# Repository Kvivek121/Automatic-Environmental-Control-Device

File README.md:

# Automatic-Environmental-Control-Device

1.Project details ---------------------------------------------------------------------1
	(– Problem Statement / Objectives / Expectations / Working principle)
2.Design consideration containing------------------------------------------------2
	a. Block diagram -----------------------------------------------------------------2
	a.Selection criteria -------------------------------------------------------------2
	b.Calculation for components ------------------------------------------------7
	c.Firmware consideration  ----------------------------------------------------7
	d.Firmware block diagram / Flow chart ------------------------------------8
	e.Test plan  --------------------------------------------------------------------10
3.Component values and part number ------------------------------------------11
4.Circuit simulation ---------------------------------------------------------------12
5.Simulation results ---------------------------------------------------------------12
6.Test Reports ----------------------------------------------------------------------14
7.Conclusion------------------------------------------------------------------------14

1.	Project details: -

•	Project Title: -Automatic Environment Control device
•	Problem Statement: - To develop an Industrial automation device which will operate certain functionalities based on the various Environmental parameters (Temperature, Pressure and Humidity level) of a Container/Room.

•	Project Objectives: - 
i.	Sense the Temperature, Humidity and Pressure from BMP280 and DHT11 sensor.
ii.	Take measure to control the Environmental parameter if the value crosses a certain limit.
iii.	Provide a functionality to user to change the Threshold values of Environmental parameters through a switch.
iv.	Display the Sensed value of temperature, Humidity, pressure.  

Working: - The Automatic environmental control device work on the principle of acquisition of sensory data from the environment and process them, based on set threshold by the user the various environmental control measures can be taken to control the environmental parameters up to the desired limit. On booting up of the device the 16x2  LCD display welcome message after this  BMP280 temperature and pressure sensor and DHT11digital  humidity and temperature sensor start sensing the various environmental parameter , STM32f103C8t6 based microcontroller communicate with the  sensors through different Communication protocols like SPI with BMP 280 and digital read for DHT 11 sensor based on the set algorithm the raw values of the sensors are converted into useful data and simultaneously the process data is displayed on the 16x2 LCD display which is using I2C  protocol for communication with the microcontroller. Sensors are directly been powered from microcontroller which is been powered by a 9 volt battery,  the user also get three switches which are used to generate interrupt the first switch is a menu switch the second switch increment the threshold and the third switch is to decrement the threshold when the user press the menu button the program enter into a menu program based on the number of times user press the menu button the functionality changes, if the user presses button once temperature threshold update menu open while for two pressure update menu and for three Humidity threshold update menu. If the user presses five times the program returns back to the Main program where the continuous measurement of the environmental parameter is taking. 
If a particular parameter viz. temperature, pressure or humidity exceeds the set threshold value, a trigger to the   relay circuitry is generated which is separated by an opto-isolator. Relay circuitry operates the environmental control measures, for example if temperature of a room increases above a set threshold value the air conditioner or a fan can be operated similarly if Humidity exceeds a certain limit dry air can be pumped in and if pressure is increased above a certain limit the Chamber can be pressurized or de-pressurized based on the requirement.
	2. Design consideration containing
	
a.	 Block diagram 

General Device Block diagram

b.	Selection criteria 
The various components are selected based on the required functionality, easy availability, cost and pression up to which the sensor can provide the output, below is the detailed selection criterion and the available alternatives in the market. 

1.	Microcontroller: - STM32f103c8t6 is used in the project to collect the sensory inputs from BMP280 and DHT11 sensor which work on SPI and digital input interfaces, while and 16X2 LCD with an I2C extender is used which uses I2C protocol for communication.
Blue pill provides SPI, I2C ports and digital I/O pins and Timers with 64KB Flash and 20KB of SRAM which satisfied the need for the application with minimum wastage of resources.
Available alternatives: - A range of Microcontrollers board by STM32, PIC, Arduino, Espressif, Raspberry pi are available. The closest alternative was the STM32f103c6t6 board but due to only 32Kbytes of Flash available the board was not capable to handle the Firmware.
2.	Sensor: - The sensors used in the project are Temperature, Humidity and Pressure sensor.

i.	Temperature -BMP280 sensor by Bosch is used which is a Barometric pressure and temperature measurement sensor. DHT11 sensor used in the project is also capable to measure temperature but BMP280’s measurements are more preferred due to its high accuracy.
Features used for selection: 
i.	Small size,
ii.	Low power requirement, 
iii.	Support of SPI communication port, 
iv.	Had high accuracy of ±0.12 hPa (typical) equivalent to ±1 m
v.	Resolution of data Pressure: 0.01 hPa (< 10 cm)
vi.	Operation range of Pressure: 300...1100 hPa
vii.	Average measurement time 5.5   msec

ii.	BMP280 sensor by Bosch is used which is a Barometric pressure and pressure measurement sensor.
Features used for selection: 
i.	Small size,
ii.	Low power requirement, 
iii.	Support of SPI communication port, 
iv.	Had high accuracy between 0 to 50 ° C
v.	Resolution of data Temperature: 0.01° C
vi.	Operation range of Temperature: -40…85°C
vii.	Average measurement time 5.5   msec

iii.	DHT11 sensor which is a digital Humidity and temperature sensor is used to measure the humidity levels in percentage. 
Features used for selection: 
i.	Operating Voltage: 3.5V to 5.5V
ii.	Operating current: 0.3mA (measuring) 60uA (standby)
iii.	Output: Serial data
iv.	Temperature Range: 0°C to 50°C
v.	Humidity Range: 20% to 90%
vi.	Resolution: Temperature and Humidity both are 16-bit
vii.	Accuracy: ±1°C and ±1%
3.	LCD: - A generic 16X2 LCD display is selected to display the measured sensor readings, in addition to it an LCD I2C extender is use to reduce the number of pins used to control the LCD. 
Features used for selection: 

i.	The operating voltage of this LCD is 4.7V-5.3V
ii.	It includes two rows where each row can produce 16-characters.
iii.	The utilization of current is 1mA with no backlight
iv.	Every character can be built with a 5×8-pixel box.

4.	5V Relay and circuitry: - A generic 5V relay which can be triggered from microcontroller and can operate small appliances which can work on up to 240V Ac with maximum 10A of current.
Features used for selection: 
i.	Normal Voltage is 5V DC
ii.	Normal Current is 70mA
iii.	AC load current Max is 10A at 250VAC or 120V AC
iv.	It includes 5-pins & designed with plastic material
v.	Operating time is 10msec
vi.	Release time is 5msec
vii.	Maximum switching is 300 operating per minute

S no.	Component	Requirement	Selected Component
1.	Microcontroller	1 SPI port, 1 I2C port and 1 Timer with 5 digital I/O pins  	Stm32f103c8t6
2.	Temperature Sensor 	Sensor able to provide Temperature reading in range of (-10 to 50)	BMP280
3.	Humidity Sensor	Sensor able to provide Humidity reading with 5% accuracy	ADA386
4.	Pressure Sensor	Sensor able to provide Pressure reading 	BMP280
5.	16X2 LCD with I2C Extender	A screen for displaying the reading.	JHD162A + PCF8574
sc6.	Relay	Able to handle heating, cooling and compression generating devices	SRD-05VDC-SL-C
7.	NPN transistor 	To facilitate in operating relay.	BC547
8.	Resistors	To resist current 	Generic
9.	Optocoupler 	To isolate relay circuitry from microcontroller and sensors, so as to protect microcontroller from rebooting. 	EL817
10.	3 Pin terminal connectors	To facilitate connect AC appliances.	KF301

11.	IC7805	To provide a regulated 5V power supply.	IC7805
12.	Push button	To provide user control facilities.	1825910-2   
13.	9V Battery	To provide power to microcontroller and sensors.	generic
14.	DC jack 	For connecting power sources to the board.	PJ-002AH
15.	Led	To indicate relay operation.	TLHG4405
16.	Freewheeling Diode	To facilitate relay circuitry.	1N4007
17.	Bug strip	To mount microcontroller.	generic
18.	Copper Clad PCB Board	To make a PCB board.	generic

c.	Calculation for components 

i.	Voltage Regulation 
In the project I have used IC 7805 for voltage regulation, there are two different circuitries which are electrically isolated from each other one is using a 9-volt battery to operate and another is using a 12-volt adaptor to operate. Circuitry consisting of relay is using an adaptor rating 12-volt 1.5 ampere and IC7805 is converting it into 5 volts, the microcontroller circuitry consisting of the sensors, the LCD screen user control switches is been operated by a 9-volt battery IC7805 is converting the 9 volts into 5 volts.
Adapter Rating 12V ,1.5A
Vin=12V
Vout= 5V with 1.5A
(Excess energy will be dissipated in form of heat.)  

ii.	Relay Circuitry 
The relay coil resistance =65 ohms
Supply voltage =5V
Relay current I = 5/65 = 0.076 or 76 mA.
Thus, the back EMF current will be much smaller than this. A 1N4007 will be perfectly able to handle this reverse current. PIV of a 1N4007 is 1000 V and the current handling capacity is 1 amp.
	A resistor of 560ohms is used at the base to limit the current to trigger the transistor.
d.	 Firmware consideration: - 

i.	Platform for code writing.
ii.	Code compilation 
iii.	Debugging feature,
iv.	Support from the company for stm32 microcontroller
v.	User interface 
vi.	Error handling
During the firmware consideration stage STMcubeIDE is used to write code in C language separate libraries are created for each functionality viz. BMP 280 sensor DHT11 sensors to display on LCD for writing the code for menu program and for debugging purpose. 
Input/Output configuration generated by the STMcubeIDE is used as well as the HAL APIs were also used to build the code for the project, references from GitHub are also taken to develop desired functionalities.
e.	Firmware block diagram / Flow chart 

f.	Test plan: -

i.	Unit testing 

S no.	Unit tests	Functionalities tested 	Remark
1.		BMP280 sensor 	Data acquisition on SPI 	Successfully able to communicate with sensor and able to read/ write its registers.
2.		BMP280 sensor	Tested the algorithm for conversion of Raw sensor data into useful values.	Used burst read to reduce the mismatch on register data and resist there overwriting 
3.		DHT11 sensor	Timer and microsecond delay generation for communication with sensor. 	Successfully able to generate the delay and communicate with sensor.
4.		LCD I2C 	Communicate with LCD I2C extender to be able to display on LCD	Used references and able to display on LCD
5.		Relay circuit	Able to trigger relay gpio of Microcontroller	Faced problem of restarting of Microcontroller when relay gets triggered due to diversion of current to coil, used opto coupler to create isolated circuitry to solve problem.
6.		Interfacing tactile push button	Able to create functionalities through push buttons	Used Interrupt to develop the functionalities. 

ii.	Integration testing
During integration testing I integrated DHT 11 sensor, BMP280 sensor, LCD i2c display and relay circuit, for integration I use the previously built libraries and called the various functions based on the requirement of functionalities. To solve the problem of diversion of current from microcontroller to relay and to stop the microcontroller from restarting while triggering the relay I used opto-coupler to isolate the relay circuitry and the microcontroller, sensor and LCD circuitry. During the testing device was accessed on the parameter of their accuracy, the sensor was providing viz DHT11 and BMP 280 and simultaneously displaying the results on the LCD display, the menu program was also tested during this integration menu button was pressed an interrupt was triggered and the program shift from the main program to the menu program and various threshold were able to be changed.
Due to not able to generate non-blocking delay the previous functionality of 15 second timer based returning from the menu program to the main program was discarded and a functionality of pressing the menu button 5 times is used to come out from the menu program come out to the main program.
3. Component values and part number 

S no.	Component	Part no	Value	Quantity
1.		Microcontroller	Stm32f103c8t6	NA	1
2.		BMP280	BMP280	NA	1
3.		DHT11	ADA386	NA	1
4.		16x2 LCD 	JHD162A
	NA	1
5.		I2C Extender	PCF8574	NA	1
6.		Relay	SRD-05VDC-SL-C		3
7.		NPN transistor 	BC547	NA	3
8.		Resistors	Generic	3- 100ohms,
3-220ohms,
3-560 ohms.	9
9.		Optocoupler 	EL817	NA	3
10.		3 Pin terminal connectors	KF301
	NA	3
11.		Voltage Regulator 	IC7805	NA	2
12.		Tactile Push button	1825910-2   	NA	3
13.		9V Battery	generic	9V	1
14.		DC jack 	PJ-002AH	NA	2
15.		Led	TLHG4405	NA	3
16.		Freewheeling Diode	1N4007	NA	3
17.		Bug strip	generic	NA	2

5.	Circuit Simulation and results 

The simulation of Relay circuitry and the power regulator circuitry is simulated on Ni Multisim tool where, the current voltages at different points are accessed virtually and working of relay circuitry is observed with switch operations from an isolated circuitry.

Simulation of hardware circuit during its testing and accessing the parameter values, shown above is the reading of DHT11 sensor and sensed Humidity is 33.53 %.

Simulation of hardware circuit during its testing and accessing the parameter values, shown above is the reading of BMP280 sensor and sensed pressure value is 976.94 hpa.

Simulation of hardware circuit during its testing and accessing the parameter values, shown above is the reading of BMP280 sensor and sensed Temperature value is 32.89-degree Celsius. The set Temperature threshold was 31 degrees, so the triggered relay circuit can be seen in the image.

6.	Test Reports 
After performing various hardware tests and simulation the firmware optimisation and system reliability was accesses and following points are noted based on the observations and findings: -
i.	The system was able to collect temperature and pressure data from BMP280 sensor, which was found to be very closed to the actual values. The pressure reading was able to be collected with an accuracy of 96.2%.  and temperature reading with difference of ±1.5% (empirically).
ii.	The measurement values from DHT11 sensor were observed and found to be stable in low turbulent space, in turbulent space the sensor take time to stabilize to a value, the accuracy of the sensor was found to be ±5to8 %.
iii.	The relay circuitry was found to source current during triggering the transistor with a pin of microcontroller, to solve this problem an opto-isolated circuitry with two power supply is used in the device.
7.	Conclusion
The device works well in compact spaces with less turbulent air, shows all the functionalities of measuring temperature, pressure and humidity and can trigger to control environmental parameters. The device is recommended to be used in cold storage applications, weather monitoring applications, HVAC application, refrigeration applications etc.

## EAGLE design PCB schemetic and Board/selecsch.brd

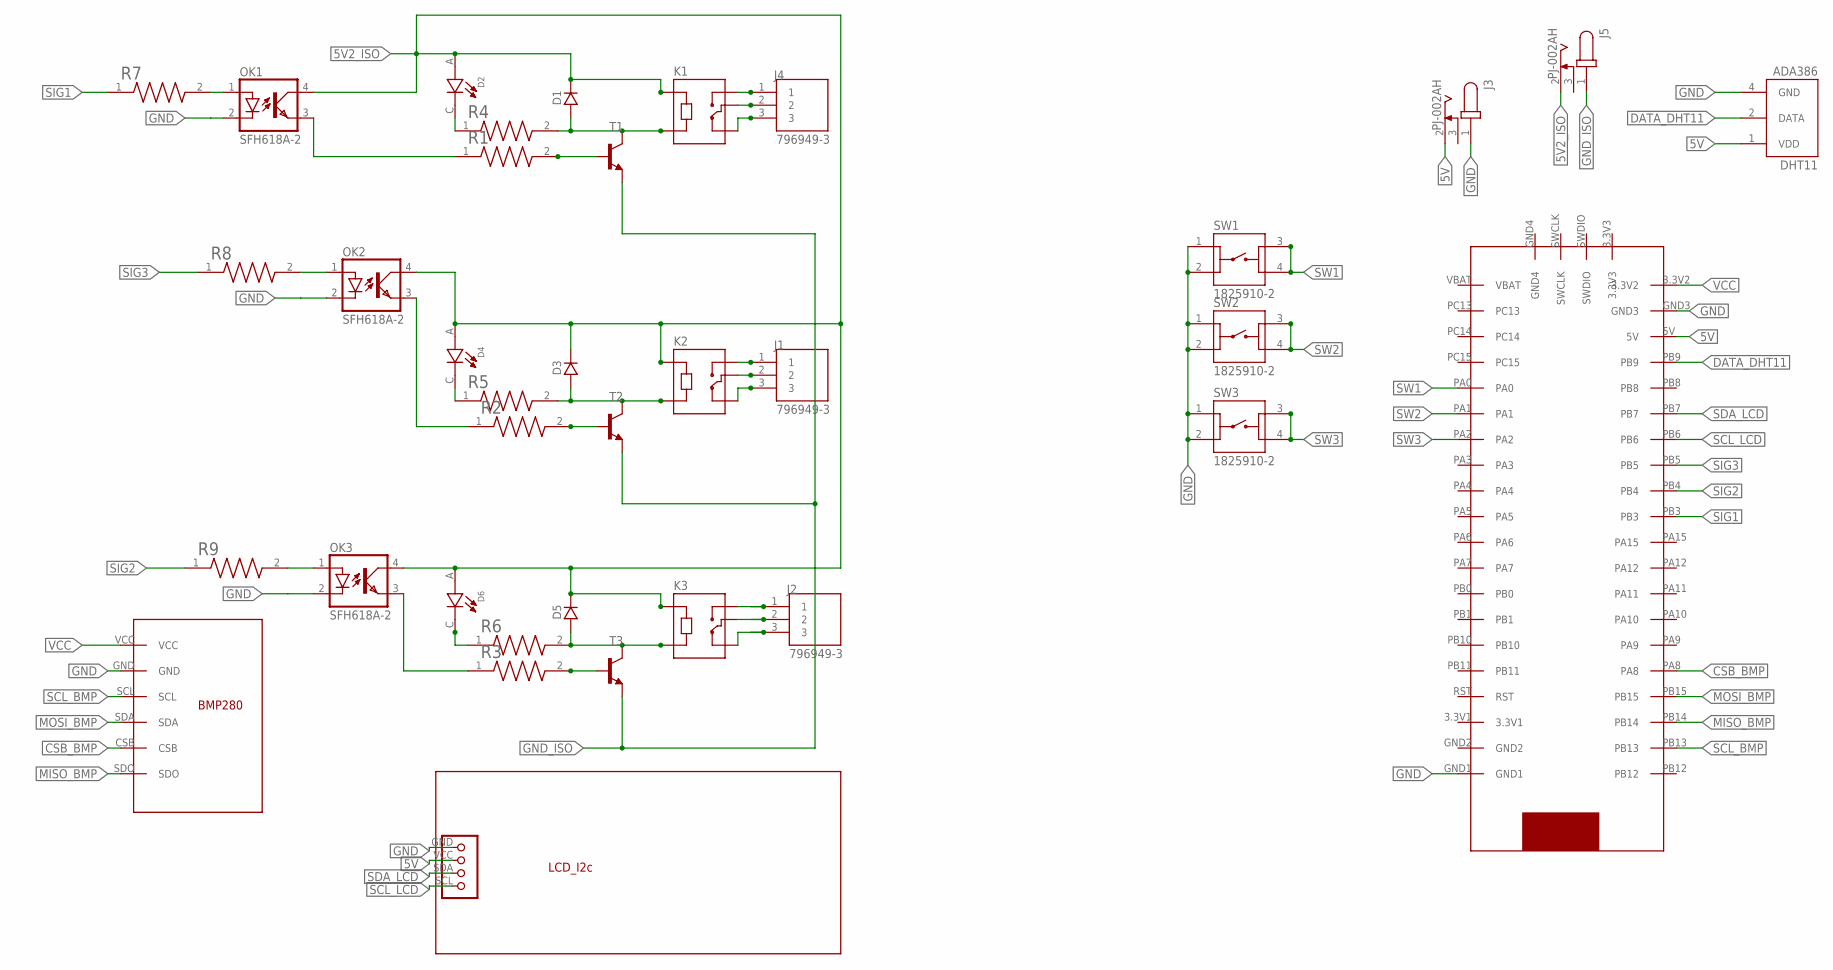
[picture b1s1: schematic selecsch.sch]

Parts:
D1, D3, D5: 1N4007; DO41
D2, D4, D6: L08R5000Q1; LEDRD254W57D500H1070
DHT11: ADA386; XDCR_ADA386
J1, J2, J4: 796949-3; TE_796949-3
J3, J5: PJ-002AH; CUI_PJ-002AH
K1, K2, K3: SRD-05VDC-SL-C; RELAY_SRD-05VDC-SL-C
LCD16X1: LCD16X2
OK1, OK2, OK3: SFH618A-2; DIP4
R1, R2, R3, R4, R5, R6, R7, R8, R9: 2-1623927-3; RESAD700W45L350D185
SW1, SW2, SW3: 1825910-2; TE_1825910-2
T1, T2, T3: BC547TO92-CBE; TO92-CBE
U$1: BMP280
U$2: STM32F103C8T6BLUEPILL

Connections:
5V: DHT11.1 (VDD), J3.2, LCD16X1.VCC, U$2.5V
5V2_ISO: D1.K, D2.A, D3.K, D4.A, D5.K, D6.A, J5.2, K1.A1, K2.A1, K3.A1, OK1.4 (COL), OK2.4 (COL), OK3.4 (COL)
CSB_BMP: U$1.CSB, U$2.PA8
DATA_DHT11: DHT11.2 (DATA), U$2.PB9
GND: DHT11.4 (GND), J3.1, LCD16X1.GND, SW1.1, SW1.2, SW2.1, SW2.2, SW3.1, SW3.2, U$1.GND, U$2.GND1, U$2.GND3
GND_ISO: J5.1, T1.E, T2.E, T3.E
MISO_BMP: U$1.SDO, U$2.PB14
MOSI_BMP: U$1.SDA, U$2.PB15
unnamed: D1.A, K1.A2, R4.2, T1.C
unnamed: R1.2, T1.B
unnamed: J4.1, K1.NO
unnamed: J4.2, K1.COM
unnamed: J4.3, K1.NC
unnamed: D3.A, K2.A2, R5.2, T2.C
unnamed: R2.2, T2.B
unnamed: J1.1, K2.NO
unnamed: D2.C, R4.1
unnamed: J1.2, K2.COM
unnamed: J1.3, K2.NC
unnamed: D5.A, K3.A2, R6.2, T3.C
unnamed: D6.C, R6.1
unnamed: R3.2, T3.B
unnamed: J2.1, K3.NO
unnamed: J2.2, K3.COM
unnamed: J2.3, K3.NC
unnamed: D4.C, R5.1
unnamed: OK1.3 (EMIT), R1.1
unnamed: OK3.3 (EMIT), R3.1
unnamed: OK1.1 (A), R7.2
unnamed: OK3.1 (A), R9.2
unnamed: OK2.1 (A), R8.2
unnamed: OK2.3 (EMIT), R2.1
SCL_BMP: U$1.SCL, U$2.PB13
SCL_LCD: LCD16X1.SCL, U$2.PB6
SDA_LCD: LCD16X1.SDA, U$2.PB7
SIG1: R7.1, U$2.PB3
SIG2: R9.1, U$2.PB4
SIG3: R8.1, U$2.PB5
SW1: SW1.3, SW1.4, U$2.PA0
SW2: SW2.3, SW2.4, U$2.PA1
SW3: SW3.3, SW3.4, U$2.PA2
VCC: U$1.VCC, U$2.3.3V2

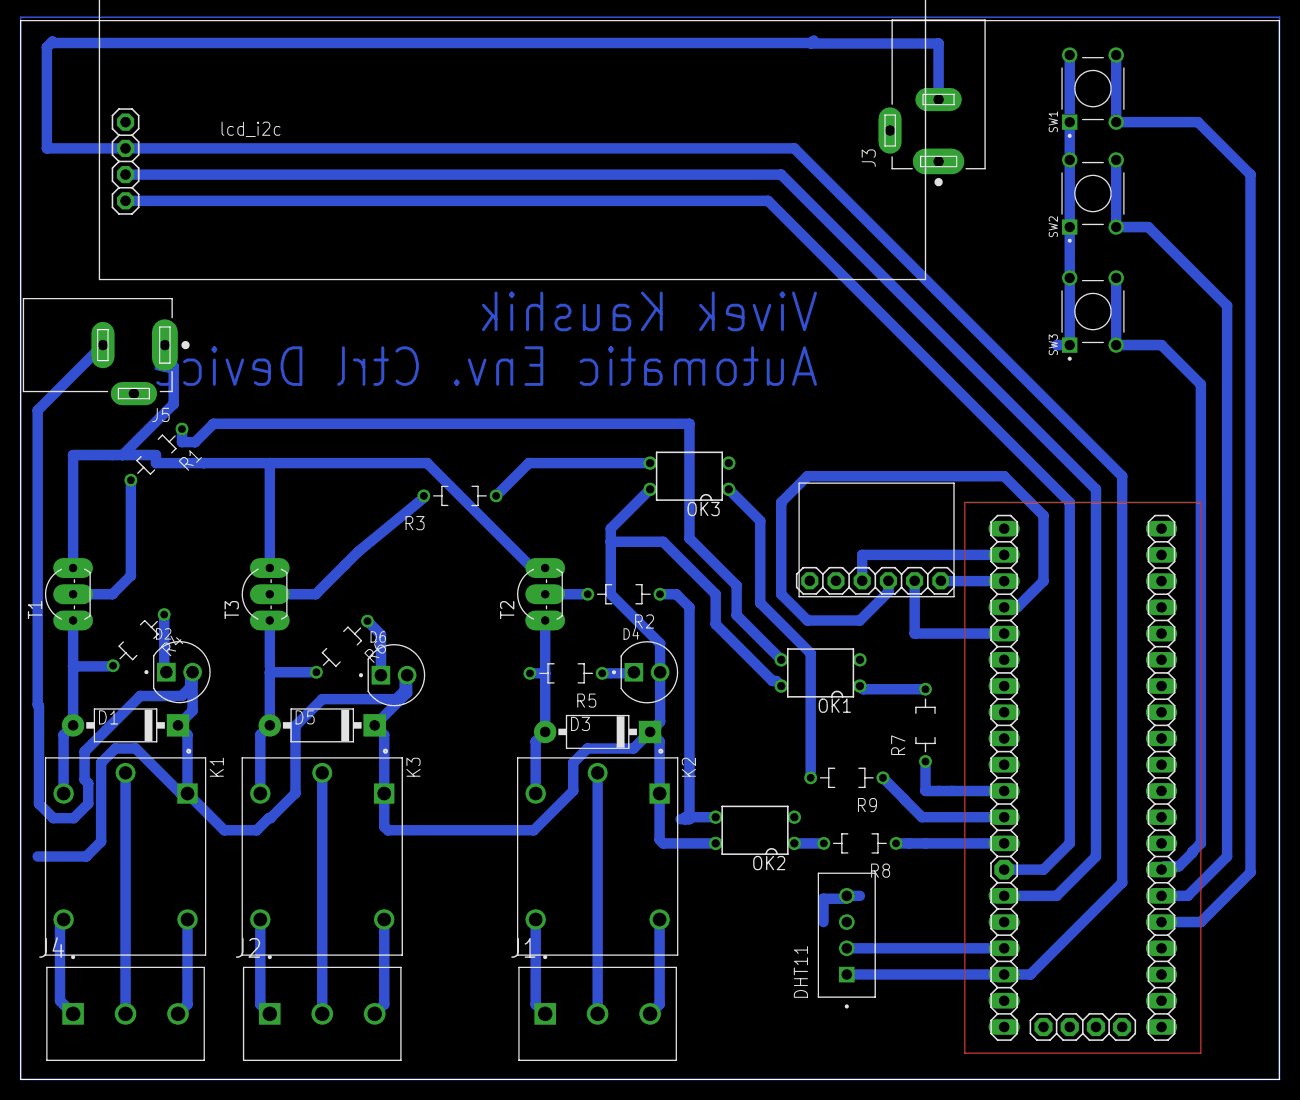
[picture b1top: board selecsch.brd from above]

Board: 2 copper layers, 121.9 x 102.5 mm, 36 parts (0 on the bottom side), 42 nets.

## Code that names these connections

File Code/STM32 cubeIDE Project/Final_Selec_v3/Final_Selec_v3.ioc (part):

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Mcu.Name=STM32F103C(8-B)Tx
Mcu.Package=LQFP48
Mcu.UserName=STM32F103C8Tx
PA0-WKUP.GPIOParameters=GPIO_PuPd,GPIO_ModeDefaultEXTI
PA0-WKUP.GPIO_ModeDefaultEXTI=GPIO_MODE_IT_FALLING
PA0-WKUP.GPIO_PuPd=GPIO_PULLUP
PA0-WKUP.Signal=GPXTI0
PA1.GPIOParameters=GPIO_PuPd,GPIO_ModeDefaultEXTI
PA1.GPIO_ModeDefaultEXTI=GPIO_MODE_IT_FALLING
PA1.GPIO_PuPd=GPIO_PULLUP
PA1.Signal=GPXTI1
PA13.Mode=Serial_Wire
PA13.Signal=SYS_JTMS-SWDIO
PA14.Mode=Serial_Wire
PA14.Signal=SYS_JTCK-SWCLK
PA2.GPIOParameters=GPIO_PuPd,GPIO_ModeDefaultEXTI
PA2.GPIO_ModeDefaultEXTI=GPIO_MODE_IT_FALLING
PA2.GPIO_PuPd=GPIO_PULLUP
PA2.Signal=GPXTI2
PA8.Signal=GPIO_Output
PB13.Mode=Full_Duplex_Master
PB13.Signal=SPI2_SCK
PB14.Mode=Full_Duplex_Master
PB14.Signal=SPI2_MISO
PB15.Mode=Full_Duplex_Master
PB15.Signal=SPI2_MOSI
PB3.GPIOParameters=PinState
PB3.PinState=GPIO_PIN_RESET
PB3.Signal=GPIO_Output
PB4.Signal=GPIO_Output
PB5.Signal=GPIO_Output
PB6.Mode=I2C
PB6.Signal=I2C1_SCL
PB7.Mode=I2C
PB7.Signal=I2C1_SDA
PB9.Signal=GPIO_Input
PD0-OSC_IN.Mode=HSE-External-Oscillator
PD0-OSC_IN.Signal=RCC_OSC_IN
PD1-OSC_OUT.Mode=HSE-External-Oscillator
PD1-OSC_OUT.Signal=RCC_OSC_OUT
RCC.SYSCLKFreq_VALUE=72000000
RCC.SYSCLKSource=RCC_SYSCLKSOURCE_PLLCLK
board=custom

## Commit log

2023-03-25 Uploading Automatic Environmental Control device
2023-03-25 Added Readme.
